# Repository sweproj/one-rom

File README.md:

# One ROM

**[One ROM](https://onerom.org) - One ROM To Rule Them All**

The most flexible ROM replacement for your retro computer.  It is highly configurable and low-cost.  Get them fabbed at JLC for under $5 each in a quantity of 10 or more.

Based on a Raspberry Pi RP2350 (One ROM Fire 🔥) or STM32F4 (One ROM Ice ❄️).

One ROM is available as 24 pin and 28 pin versions, emulating nearly all systems' 24 and 28 pin ROMs, including any possible chip select configurations with a single hardware variants, and can serve different images to multiple ROM sockets simultaneously.

Replaces failed ROMs in Commodore 64s, VIC-20s, PETs, Ataris, BBC, TIs, disk drives and many other types of systems, like pinball machines and music synthesizers.

ROM types replaced:
- 24 pin: 2704, 2708, 2716, 2732, 2316, 2332, 2364
- 28 pin: 2764, 27128, 27256, 27512, 23128, 23256, 23512

As of the latest firmware, One ROM also supports RAM chips of the correct footprint, including the 6116 and 2016 2K SRAM chips.

One ROM was formerly known as Software Defined Retro ROM (SDRR).

## Quick Start

See https://onerom.org/start/

## Key Features

💰 Based on sub-$2 microcontrollers.  **[Choose from Raspberry Pi (Fire 🔥) or STM (Ice ❄️) flavours](docs/MCU-SELECTION.md)**.

⚡ **[Fast](docs/STM32-SELECTION.md)** enough for PETs, VIC-20s, C64s, 1541s, IEEE drives, etc. Support faster systems with higher end microcontroller.

📐 **[Same footprint](docs/images/sdrr-24-pin-side.png)** as original ROMs - doesn't overhang the socket like other solutions.

🔌 **[USB Version](https://onerom.org/prog/)** - no programmer required, program from your browser.

🚀 **[Quick programming](docs/PROGRAMMING.md)** - build and flash in <10 seconds.

🛠️ **[Reflash in situ](docs/PROGRAMMING.md)** - no need to remove the ROM from the host when reprogramming.

⚙️ **[Software configurable](docs/CONFIGURATION.md)** chip select lines - no hardware jumpers required.

💾 Stores up to **[16 ROM images](docs/STM32-SELECTION.md)** of different sizes and chip select configurations.  Image selectable via jumpers.

📦 **[Replace multiple ROMs with one ROM](docs/MULTI-ROM-SETS.md)** a single One ROM can replace up to 3 original ROMs e.g. all of C64 kernel, BASIC, character set.

🔀 **[Dynamic bank switching](docs/MULTI-ROM-SETS.md)** - switch between ROM images on the fly, e.g. different char ROMs.

💻 **[Hackable at runtime](docs/RUNTIME-ACCESS.md)** - change the ROM images being served and access telemetry from the ROM at runtime using **[Airfrog](https://piers.rocks/u/airfrog)** or other SWD probes.

🧩 **[Images combined automatically](docs/CONFIGURATION.md)** - no need to manually build up your own larger PROM image containing multiple retro ROMs.

🏭 **[Two layer PCB](sdrr-pcb/README.md)**, component on single-side, limited BOM for low manufacturing cost/complexity.

🎯 Supports multiple **[STM32F4xxR](docs/STM32-SELECTION.md)** variants: F401, F411, F405, F446 (others can be added).

🔓 **[Open source](LICENSE.md)** software and hardware.

## Introduction

The video below provides an introduction to One ROM:

## Hardware

This is the Fire 24-pin version, hardware revison A.  See [sdrr-pcb](sdrr-pcb/README.md) for the hardware designs and documentation.

<div style="display: flex; justify-content: center; gap: 20px;">
  
</div>

## Documentation

| Topic | Description |
|-------|-------------|
| [Getting Started](docs/GETTING-STARTED.md) | Detailed instructions for flashing your One ROM |
| [Frequently Asked Questions](docs/FAQ.md) | Answers to common questions about One ROM. |
| [Installation](INSTALL.md) | Installation of dependencies. |
| [Programming](docs/PROGRAMMING.md) | How to program One ROM. |
| [Available Configurations](config/README.md#available-configurations) | Various pre-collated ROM collection configurations. |
| [MCU Selection](docs/MCU-SELECTION.md) | How to select the appropriate MCU for your application. |
| [Image Selection](docs/IMAGE-SELECTION.md) | How to tell One ROM which of the installed ROM images to serve. |
| [Image Sets](docs/MULTI-ROM-SETS.md) | How to use a single One ROM to support multiple ROMs simultaneously or to dynamically switch between images. |
| [Configuration](docs/CONFIGURATION.md) | One ROM configuration options. |
| [Runtime Access/Control](docs/RUNTIME-ACCESS.md) | Access and control the One ROM while it is serving ROMs. |
| [Compatibility](docs/COMPATIBILITY.md) | Compatibility with various retro systems. |
| [Logging](docs/LOGGING.md) | How to enable and use One ROM logging. |
| [Technical Summary](docs/TECHNICAL-SUMMARY.md) | Overview of the One ROM architecture, operation and design decisions. |
| [Technical Details](docs/TECHNICAL-DETAILS.md) | Technical details of the One ROM firmware and hardware. |
| [ROMs Glorious ROMs](docs/ROMS-GLORIOUS-ROMS.md) | Everything you ever wanted to know about 23/27 series ROMs but were afraid to ask. |
| [Custom Hardware](docs/CUSTOM-HARDWARE.md) | Guide on designing custom hardware for One ROM. |
| [Build System](docs/BUILD-SYSTEM.md) | How the One ROM build system works. |
| [Voltage Levels](docs/VOLTAGE-LEVELS.md) | How the One ROM supports the required logic voltage levels. |
| [Pi Pico Programmer](docs/PI-PICO-PROGRAMMER.md) | How to use a $5 Raspberry Pi Pico as a programmer for One ROM. |
| [Manufacturing Test](docs/MANUFACTURING-TEST.md) | Information on testing One ROM during manufacturing. |
| [STM32 Clones](docs/STM32-CLONES.md) | Information using STM32 clones with One ROM. |
| [Future Enhancements](docs/FUTURE-ENHANCEMENTS.md) | Possible future enhancements under consideration. |
| [License](LICENSE.md) | One ROM software and hardware licenses. |

## Debugging

The best place to start with debugging is [`Logging`](docs/LOGGING.md).  This will help you see what the One ROM is doing, and why it may not be working as expected.

If you have an [Airfrog](https://piers.rocks/u/airfrog), you can use it to inspect the One ROM firmware and its current state.

If you'd like a hand, raise an issue on the [GitHub issues page](https://github.com/piersfinlayson/software-defined-retro-rom/issues).  Please provide:

- the MCU you are using and the PCB type/revision
- the retro system you are trying to One ROM with
- any logging from One ROM
- ideally, the firmware image, if you are happy to share.

If you have built the firmware yourself, rather than using a pre-built release image, also provide:

- your build configuration
- the output from `make info-detail`.

## License

See [LICENSE](LICENSE.md) for software and hardware licensing information.

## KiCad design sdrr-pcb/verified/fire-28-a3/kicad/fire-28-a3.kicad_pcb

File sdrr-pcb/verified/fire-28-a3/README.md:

# One ROM Fire 28 pin 

**Verified - This design only differs from A2 in correcting the SWD CLK/DIO silkscreen labels.

A3 revision of the 28 pin Fire ROM board.  Combined USB/Pro version with USB-C and SWD header pins.

Very minor difference from revision A2:
- CLK/DIO silkscreen labels swapped to correct positions.

## Contents

- [Schematic](./fire-28-a3-schematic.pdf)
- [Fab Files](fab/)
- [KiCad Design Files](kicad/)
- [Errata](#errata)
- [Notes](#notes)
- [Changelog](#changelog)
- [BOM](#bom)

## Errata

## Notes

## Changelog

## BOM

See fab files.

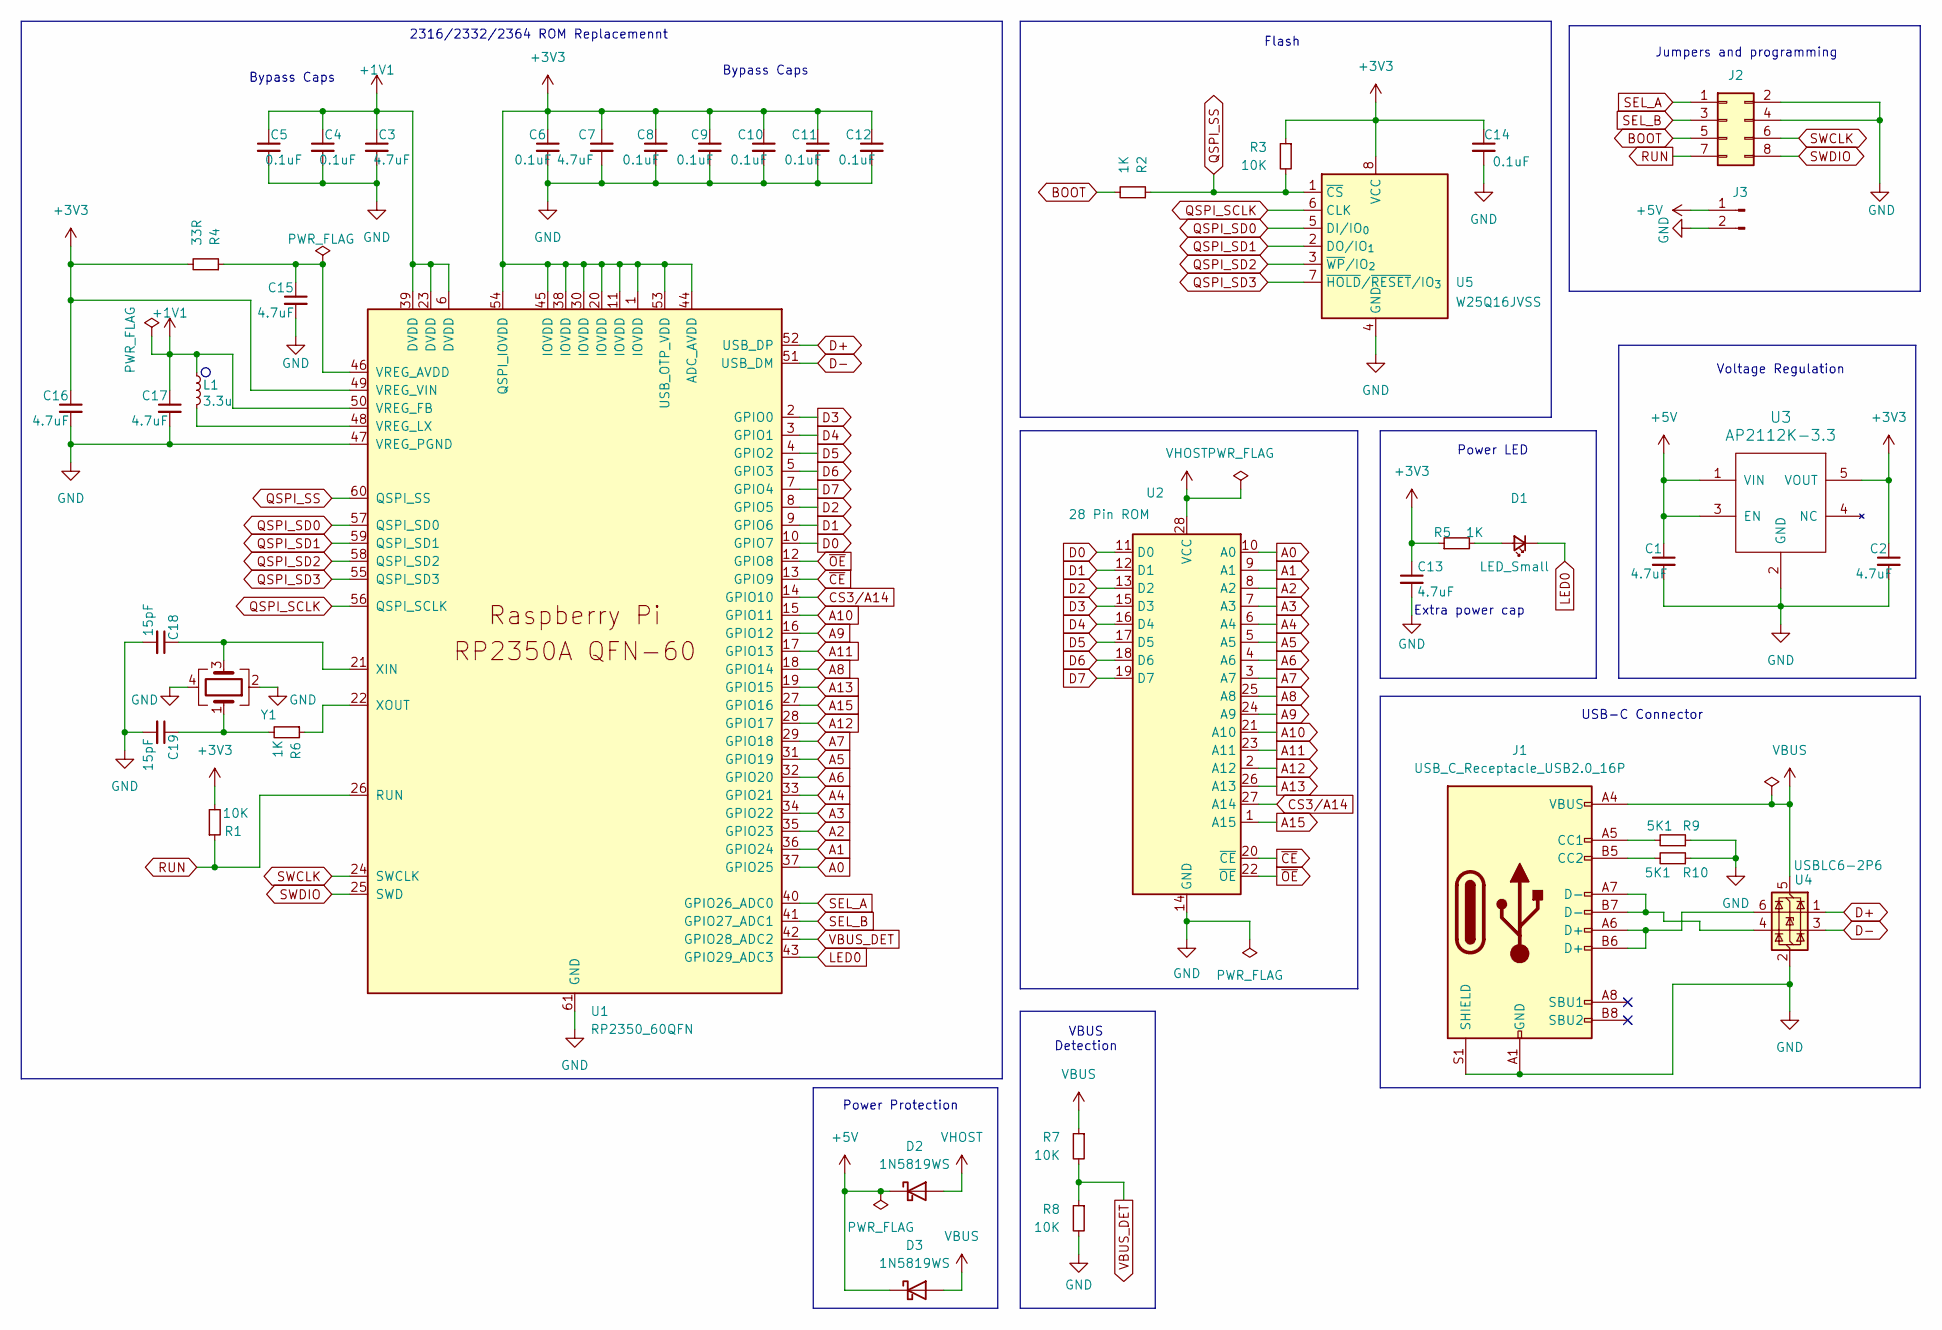
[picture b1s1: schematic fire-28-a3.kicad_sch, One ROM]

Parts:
C1, C2, C3, C7, C13, C15: 4.7uF; C_0402_1005Metric; LCSC C23733
C4, C5, C6, C8, C9, C10, C11, C12, C14: 0.1uF; C_0402_1005Metric; LCSC C1525
C16, C17: 4.7uF; C_0402_1005Metric_small_pads; LCSC C23733
C18, C19: 15pF; C_0402_1005Metric; LCSC C1548
D1: LED_Small; LED_0603_1608Metric; LCSC C2286
D2, D3: 1N5819WS; D_SOD-323; LCSC C191023
J1: USB_C_Receptacle_USB2.0_16P; USB_C_connector_c2765186; LCSC C2765186
J2: Conn_02x04_Odd_Even; PinHeader_2x04_P2.54mm_Vertical custom silkscreen
J3: Conn_01x02_Pin; PinHeader_1x02_P2.54mm_Vertical
L1: 3.3u; L_pol_2016; LCSC C42411119
R1, R3, R7, R8: 10K; R_0402_1005Metric; LCSC C25744
R2, R5, R6: 1K; R_0402_1005Metric; LCSC C11702
R4: 33R; R_0402_1005Metric; LCSC C25105
R9, R10: 5K1; R_0402_1005Metric; LCSC C25905
U1: RP2350_60QFN; RP2350-QFN-60-1EP_7x7_P0.4mm_EP3.4x3.4mm_ThermalVias; LCSC C42411118
U2: 28 Pin ROM; 28 pin rom footprint
U3: AP2112K-3.3; SOT-23-5; LCSC C51118
U4: USBLC6-2P6; SOT-666; LCSC C15999
U5: W25Q16JVSS; Winbond_USON-8-1EP_3x2mm_P0.5mm_EP0.2x1.6mm; LCSC C2843335
Y1: Crystal_GND24; Crystal_SMD_Abracon_ABM8G-4Pin_3.2x2.5mm; LCSC C20625731

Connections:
+1V1: C3.1, C4.1, C5.1, C17.1, L1.1, U1.6 (DVDD), U1.23 (DVDD), U1.39 (DVDD), U1.50 (VREG_FB)
+3V3: C2.1, C6.1, C7.1, C8.1, C9.1, C10.1, C11.1, C12.1, C13.1, C14.1, C16.1, R1.2, R3.1, R4.2, R5.1, U1.1 (IOVDD), U1.11 (IOVDD), U1.20 (IOVDD), U1.30 (IOVDD), U1.38 (IOVDD), U1.44 (ADC_AVDD), U1.45 (IOVDD), U1.49 (VREG_VIN), U1.53 (USB_OTP_VDD), U1.54 (QSPI_IOVDD), U3.5 (VOUT), U5.8 (VCC)
+5V: C1.1, D2.1 (K), D3.1 (K), J3.1, U3.1 (VIN), U3.3 (EN)
A0: U1.37 (GPIO25), U2.10 (A0)
A1: U1.36 (GPIO24), U2.9 (A1)
A2: U1.35 (GPIO23), U2.8 (A2)
A3: U1.34 (GPIO22), U2.7 (A3)
A4: U1.33 (GPIO21), U2.6 (A4)
A5: U1.31 (GPIO19), U2.5 (A5)
A6: U1.32 (GPIO20), U2.4 (A6)
A7: U1.29 (GPIO18), U2.3 (A7)
A8: U1.18 (GPIO14), U2.25 (A8)
A9: U1.16 (GPIO12), U2.24 (A9)
A10: U1.15 (GPIO11), U2.21 (A10)
A11: U1.17 (GPIO13), U2.23 (A11)
A12: U1.28 (GPIO17), U2.2 (A12)
A13: U1.19 (GPIO15), U2.26 (A13)
A15: U1.27 (GPIO16), U2.1 (A15)
BOOT: J2.5, R2.2
CS3/A14: U1.14 (GPIO10), U2.27 (A14)
D0: U1.10 (GPIO7), U2.11 (D0)
D1: U1.9 (GPIO6), U2.12 (D1)
D2: U1.8 (GPIO5), U2.13 (D2)
D3: U1.2 (GPIO0), U2.15 (D3)
D4: U1.3 (GPIO1), U2.16 (D4)
D5: U1.4 (GPIO2), U2.17 (D5)
D6: U1.5 (GPIO3), U2.18 (D6)
D7: U1.7 (GPIO4), U2.19 (D7)
D+: U1.52 (USB_DP), U4.1 (I/O1)
D-: U1.51 (USB_DM), U4.3 (I/O2)
GND: C1.2, C2.2, C3.2, C4.2, C5.2, C6.2, C7.2, C8.2, C9.2, C10.2, C11.2, C12.2, C13.2, C14.2, C15.2, C16.2, C17.2, C18.2, C19.2, J1.A1 (GND), J1.A12 (GND), J1.B1 (GND), J1.B12 (GND), J1.S1 (SHIELD), J2.2, J2.4, J3.2, R8.2, R9.1, R10.1, U1.47 (VREG_PGND), U1.61 (GND), U2.14 (GND), U3.2 (GND), U4.2 (GND), U5.4 (GND), Y1.2, Y1.4
LED0: D1.1 (K), U1.43 (GPIO29_ADC3)
unnamed: C19.1, R6.2, Y1.1
unnamed: D1.2 (A), R5.2
unnamed: J1.A5 (CC1), R9.2
unnamed: J1.B5 (CC2), R10.2
unnamed: J1.A6 (D+), J1.B6 (D+), U4.6 (I/O1)
unnamed: J1.A7 (D-), J1.B7 (D-), U4.4 (I/O2)
unnamed: C15.1, R4.1, U1.46 (VREG_AVDD)
unnamed: L1.2, U1.48 (VREG_LX)
unnamed: C18.1, U1.21 (XIN), Y1.3
unnamed: R6.1, U1.22 (XOUT)
QSPI_SCLK: U1.56 (QSPI_SCLK), U5.6 (CLK)
QSPI_SD0: U1.57 (QSPI_SD0), U5.5 (DI/IO_{0})
QSPI_SD1: U1.59 (QSPI_SD1), U5.2 (DO/IO_{1})
QSPI_SD2: U1.58 (QSPI_SD2), U5.3 (~WP/IO_{2})
QSPI_SD3: U1.55 (QSPI_SD3), U5.7 (~HOLD/~RESET/IO_{3})
QSPI_SS: R2.1, R3.2, U1.60 (QSPI_SS), U5.1 (~CS)
RUN: J2.7, R1.1, U1.26 (RUN)
SEL_A: J2.1, U1.40 (GPIO26_ADC0)
SEL_B: J2.3, U1.41 (GPIO27_ADC1)
SWCLK: J2.6, U1.24 (SWCLK)
SWDIO: J2.8, U1.25 (SWD)
VBUS: D3.2 (A), J1.A4 (VBUS), J1.A9 (VBUS), J1.B4 (VBUS), J1.B9 (VBUS), R7.1, U4.5 (VBUS)
VBUS_DET: R7.2, R8.1, U1.42 (GPIO28_ADC2)
VHOST: D2.2 (A), U2.28 (VCC)
~CE: U1.13 (GPIO9), U2.20 (~CE)
~OE: U1.12 (GPIO8), U2.22 (~OE)

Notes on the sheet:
USB-C Connector
Voltage Regulation
Extra power cap
2316/2332/2364 ROM Replacemennt
Bypass Caps
Power LED
Power Protection
VBUS Detection
Flash
Jumpers and programming

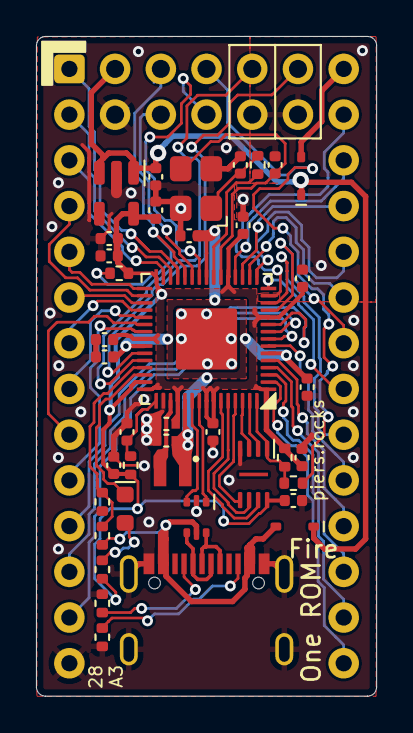
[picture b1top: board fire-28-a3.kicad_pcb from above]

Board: 2 copper layers, 18.9 x 36.7 mm, 42 parts (0 on the bottom side), 58 nets.

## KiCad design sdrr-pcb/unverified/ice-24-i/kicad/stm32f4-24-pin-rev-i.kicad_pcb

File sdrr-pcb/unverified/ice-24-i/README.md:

# One ROM Ice USB H2 24 Pin 

**Unverified**: Similar to ice-24-c.

There is a single set of gerbers, and two sets of POS/BOM files:
- One for the STM32F411RET6 MCU.
- One for the STM32F446RCT6 MCU.

To create the BOM for an alternate MCU, replace the microcontroller part number.  For the STM32F405RET6, you must also replace RC4/RC5/C9 - see the schematic for details.

## Contents

- [Schematic](ice-24-i-schematic.pdf)
- [Fab Files and BOM](fab/)
- [KiCad Design Files](kicad/)
- [Errata](#errata)
- [Notes](#notes)
- [Changelog](#changelog)

## Errata

## Notes

## Changelog

- Move to 1N5819 diodes from MSK4005 (better availability and JLC basic part)
- Moved programming header to top left, replacing Sel pins C-E
- Reduced rom pin hole and ring size
- Reduced silkscreen markings on the top side

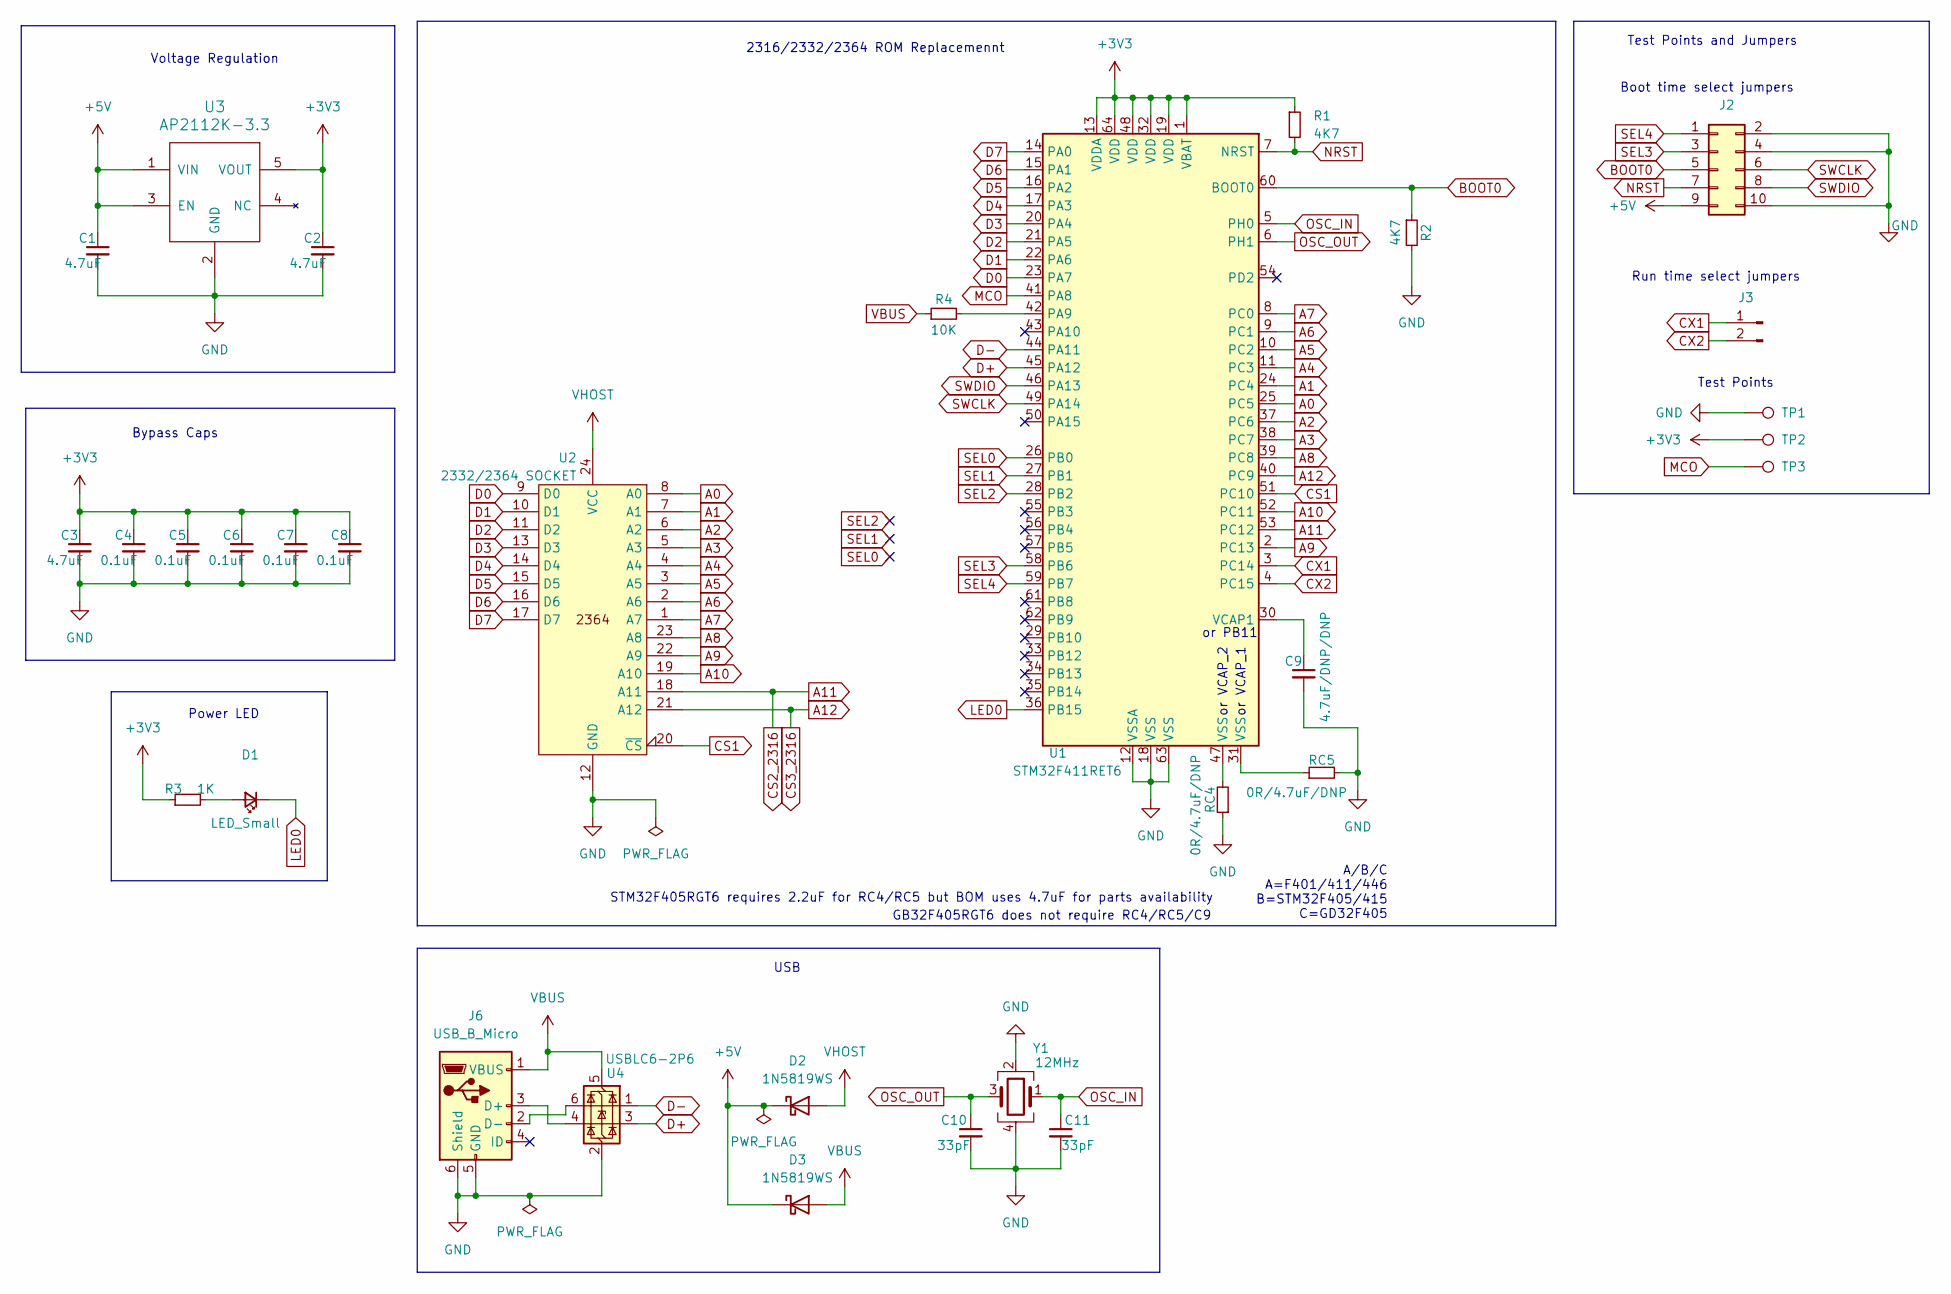
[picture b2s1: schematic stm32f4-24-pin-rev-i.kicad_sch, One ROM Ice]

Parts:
C1, C2, C3: 4.7uF; C_0402_1005Metric; LCSC C23733
C4, C5, C6, C7, C8: 0.1uF; C_0402_1005Metric; LCSC C1525
C9: 4.7uF/DNP/DNP; C_0402_1005Metric; LCSC C23733
C10, C11: 33pF; C_0402_1005Metric; LCSC C1562
D1: LED_Small; LED_0603_1608Metric; LCSC C2286
D2, D3: 1N5819WS; D_SOD-323; LCSC C191023
J2: Conn_02x05_Odd_Even; PinHeader_2x05_P2.54mm_Vertical custom silkscreen
J3: Conn_01x02_Pin; PinHeader_1x02_P2.54mm_Vertical
J6: USB_B_Micro; USB_Micro-B_micro_xnj_073_C404969; LCSC C404969
R1, R2: 4K7; R_0402_1005Metric; LCSC C25900
R3: 1K; R_0402_1005Metric; LCSC C11702
R4: 10K; R_0402_1005Metric; LCSC C25744
RC4, RC5: 0R/4.7uF/DNP; C_0402_1005Metric; LCSC C17168
TP1, TP2, TP3: TestPoint; 1mm smd test point small ss
U1: STM32F411RET6; LQFP-64_10x10mm_P0.5mm; LCSC C94355
U2: 2332/2364 SOCKET; 2x12 dip pin output 600mil centres no ss
U3: AP2112K-3.3; SOT-23-5; LCSC C51118
U4: USBLC6-2P6; SOT-666; LCSC C15999
Y1: 12MHz; Crystal_SMD_3225-4Pin_3.2x2.5mm; LCSC C9002

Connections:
+3V3: C2.1, C3.1, C4.1, C5.1, C6.1, C7.1, C8.1, R1.1, R3.1, TP2.1, U1.1 (VBAT), U1.13 (VDDA), U1.19 (VDD), U1.32 (VDD), U1.48 (VDD), U1.64 (VDD), U3.5 (VOUT)
+5V: C1.1, D2.1 (K), D3.1 (K), J2.9, U3.1 (VIN), U3.3 (EN)
A0: U1.25 (PC5), U2.8 (A0)
A1: U1.24 (PC4), U2.7 (A1)
A2: U1.37 (PC6), U2.6 (A2)
A3: U1.38 (PC7), U2.5 (A3)
A4: U1.11 (PC3), U2.4 (A4)
A5: U1.10 (PC2), U2.3 (A5)
A6: U1.9 (PC1), U2.2 (A6)
A7: U1.8 (PC0), U2.1 (A7)
A8: U1.39 (PC8), U2.23 (A8)
A9: U1.2 (PC13), U2.22 (A9)
A10: U1.52 (PC11), U2.19 (A10)
A11: U1.53 (PC12), U2.18 (A11)
A12: U1.40 (PC9), U2.21 (A12)
BOOT0: J2.5, R2.1, U1.60 (BOOT0)
CS1: U1.51 (PC10), U2.20 (~CS)
CX1: J3.1, U1.3 (PC14)
CX2: J3.2, U1.4 (PC15)
D0: U1.23 (PA7), U2.9 (D0)
D1: U1.22 (PA6), U2.10 (D1)
D2: U1.21 (PA5), U2.11 (D2)
D3: U1.20 (PA4), U2.13 (D3)
D4: U1.17 (PA3), U2.14 (D4)
D5: U1.16 (PA2), U2.15 (D5)
D6: U1.15 (PA1), U2.16 (D6)
D7: U1.14 (PA0), U2.17 (D7)
D+: U1.45 (PA12), U4.3 (I/O2)
D-: U1.44 (PA11), U4.1 (I/O1)
GND: C1.2, C2.2, C3.2, C4.2, C5.2, C6.2, C7.2, C8.2, C9.2, C10.2, C11.2, J2.2, J2.4, J2.10, J6.5 (GND), J6.6 (Shield), R2.2, RC4.1, RC5.2, TP1.1, U1.12 (VSSA), U1.18 (VSS), U1.63 (VSS), U2.12 (GND), U3.2 (GND), U4.2 (GND), Y1.2, Y1.4
LED0: D1.1 (K), U1.36 (PB15)
MCO: TP3.1, U1.41 (PA8)
NRST: J2.7, R1.2, U1.7 (NRST)
unnamed: D1.2 (A), R3.2
unnamed: J6.3 (D+), U4.4 (I/O2)
unnamed: J6.2 (D-), U4.6 (I/O1)
unnamed: RC4.2, U1.47 (VSS)
unnamed: RC5.1, U1.31 (VSS)
unnamed: R4.2, U1.42 (PA9)
unnamed: C9.1, U1.30 (VCAP1)
OSC_IN: C11.1, U1.5 (PH0), Y1.1
OSC_OUT: C10.1, U1.6 (PH1), Y1.3
SEL0: U1.26 (PB0)
SEL1: U1.27 (PB1)
SEL2: U1.28 (PB2)
SEL3: J2.3, U1.58 (PB6)
SEL4: J2.1, U1.59 (PB7)
SWCLK: J2.6, U1.49 (PA14)
SWDIO: J2.8, U1.46 (PA13)
VBUS: D3.2 (A), J6.1 (VBUS), R4.1, U4.5 (VBUS)
VHOST: D2.2 (A), U2.24 (VCC)

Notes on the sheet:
or VCAP_1
or VCAP_2
Run time select jumpers
USB
Voltage Regulation
2316/2332/2364 ROM Replacemennt
Power LED
or PB11
GB32F405RGT6 does not require RC4/RC5/C9
Test Points
Bypass Caps
Boot time select jumpers
A/B/C A=F401/411/446 B=STM32F405/415 C=GD32F405
Test Points and Jumpers
STM32F405RGT6 requires 2.2uF for RC4/RC5 but BOM uses 4.7uF for parts availability

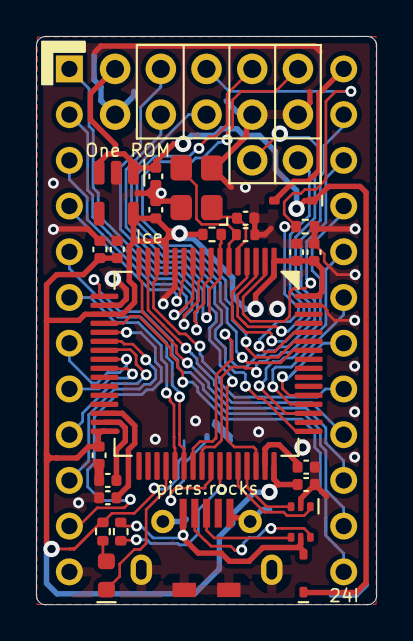
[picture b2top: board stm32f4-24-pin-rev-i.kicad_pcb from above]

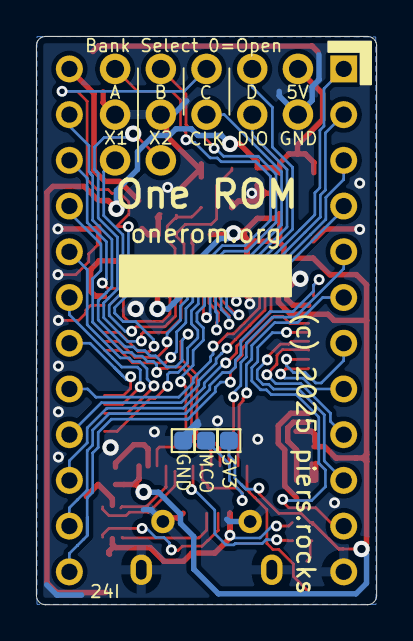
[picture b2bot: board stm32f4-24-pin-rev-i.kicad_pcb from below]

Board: 2 copper layers, 18.9 x 31.6 mm, 31 parts (3 on the bottom side), 48 nets.

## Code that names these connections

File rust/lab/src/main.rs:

//! One ROM Lab firmware

// Copyright (c) 2025 Piers Finlayson <piers@piers.rocks>
//
// MIT licence

#![no_std]
#![no_main]
#![feature(type_alias_impl_trait)]
#![feature(impl_trait_in_assoc_type)]

extern crate alloc;

#[allow(unused_imports)]
use log::{debug, error, info, trace, warn};

use embassy_executor::Spawner;
use embassy_executor::main as embassy_main;
use embassy_stm32::gpio::Flex;
use embassy_stm32::rcc::clocks;

#[cfg(feature = "repeat")]
use embassy_time::Timer;

use embedded_alloc::LlffHeap as Heap;
#[cfg(feature = "usb")]
use panic_probe as _;
#[cfg(not(feature = "usb"))]
use panic_rtt_target as _;

#[cfg(feature = "control")]
mod control;
mod error;
mod info;
mod logs;
mod rcc;
mod rom;
mod types;
#[cfg(feature = "usb")]
mod usb;

pub use error::Error;
pub use rom::{Id as RomId, Rom};

use info::{LAB_RAM_INFO, PKG_VERSION};

#[global_allocator]
static HEAP: Heap = Heap::empty();

#[cortex_m_rt::pre_init]
unsafe fn pre_init() {
    #[cfg(feature = "usb")]
    usb::check_bootloader_flag();
    info::copy_lab_ram_info();
}

#[embassy_main]
async fn main(_spawner: Spawner) {
    // Initialize the heap allocator
    {
        use core::mem::MaybeUninit;
        const HEAP_SIZE: usize = 1024;
        static mut HEAP_MEM: [MaybeUninit<u8>; HEAP_SIZE] = [MaybeUninit::uninit(); HEAP_SIZE];
        unsafe { HEAP.init(&raw mut HEAP_MEM as usize, HEAP_SIZE) }
    }

    // Set up clock config
    let mut config = embassy_stm32::Config::default();
    #[cfg(feature = "usb")]
    rcc::configure_hse_usb(&mut config);
    #[cfg(not(feature = "usb"))]
    rcc::configure_hsi(&mut config);

    // Get peripherals
    let p = embassy_stm32::init(config);

    // Configure clocks
    let clocks = clocks(&p.RCC);

    // Init USB/logging
    #[cfg(feature = "usb")]
    {
        let usb_device = usb::Usb::new(p.USB_OTG_FS, p.PA12, p.PA11);
        usb::run(_spawner, usb_device);
        usb::init_logger();
    }
    #[cfg(not(feature = "usb"))]
    logs::init_rtt();

    info!("-----");
    info!("One ROM Lab v{}", PKG_VERSION);
    info!("Copyright (c) 2025 Piers Finlayson");

    // Log clocks
    info!("-----");
    match clocks.sys.to_hertz() {
        Some(hz) => debug!("SYSCLK: {hz}"),
        None => warn!("SYSCLK: Unknown"),
    }

    debug!(
        "One ROM Lab Flash Info address: {:#010X}",
        &info::LAB_FLASH_INFO as *const _ as usize
    );
    #[allow(static_mut_refs)]
    unsafe {
        debug!(
            "One ROM Lab RAM Info address:   {:#010X}",
            &LAB_RAM_INFO as *const _ as usize
        );
    }

    // Collate the address and data pins
    let addr_pins = [
        Flex::new(p.PC5),
        Flex::new(p.PC4),
        Flex::new(p.PC6),
        Flex::new(p.PC7),
        Flex::new(p.PC3),
        Flex::new(p.PC2),
        Flex::new(p.PC1),
        Flex::new(p.PC0),
        Flex::new(p.PC8),
        Flex::new(p.PC13),
        Flex::new(p.PC11),
        Flex::new(p.PC12),
        Flex::new(p.PC9),
        Flex::new(p.PC10), // 2364 CS pin, set as "A13"
    ];
    let data_pins = [
        Flex::new(p.PA7),
        Flex::new(p.PA6),
        Flex::new(p.PA5),
        Flex::new(p.PA4),
        Flex::new(p.PA3),
        Flex::new(p.PA2),
        Flex::new(p.PA1),
        Flex::new(p.PA0),
    ];

    // Create the ROM object
    let mut rom = Rom::new(addr_pins, data_pins);
    unsafe {
        LAB_RAM_INFO.rom_data = rom.buf.as_ptr() as *const core::ffi::c_void;
    }
    rom.init();

    #[cfg(feature = "control")]
    {
        let mut control = control::Control::new(rom);
        control.run().await;
    }

    #[cfg(feature = "qa")]
    {
        info!("QA mode");
        #[cfg(feature = "usb")]
        info!("Press `d` to enter DFU mode");
        loop {
            #[cfg(not(feature = "usb"))]
            match rom.read_rom().await {
                Some(_) => info!("ROM read successfully"),
                None => info!("Failed to read ROM"),
            }
            #[cfg(feature = "usb")]
            match embassy_time::with_timeout(embassy_time::Duration::from_secs(5), usb::recv_key())
                .await
            {
                Ok(key) => {
                    if key == b'd' {
                        info!("Entering DFU mode...");
                        usb::enter_dfu_mode().await;
                    }
                }
                Err(_) => (),
            }
            #[cfg(not(feature = "usb"))]
            embassy_time::Timer::after_secs(5).await;
            info!("Reading ROM...");
        }
    }

    #[cfg(not(any(feature = "control", feature = "qa")))]
    {
        loop {
            match rom.read_rom().await {
                Some(_) => break,
                None => info!("Failed to read ROM"),
            }

            #[cfg(feature = "oneshot")]
            {
                info!("Done");
                return;
            }
            #[cfg(feature = "repeat")]
            {
                info!("Waiting 5 seconds before reading again");
                Timer::after_secs(5).await;
            }
        }
    }
}

#[cfg(all(feature = "control", feature = "oneshot"))]
compile_error!("Features 'control' and 'oneshot' are mutually exclusive");

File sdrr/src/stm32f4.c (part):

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    }
}

// Set up interrupt to fire when VBUS sensed on PA9
void setup_vbus_interrupt(void) {
    // Does NOT currently honour configured VBUS port/pin - assumes PA9
    if (sdrr_info.extra->vbus_pin != 9 ||
        sdrr_info.extra->usb_port != PORT_A) {
        LOG("!!! Invalid USB port or pin for VBUS detect - not enabling USB DFU");
        return;
    }

    // Set PA9 pull-down
    GPIOA_PUPDR &= ~(0b11 << (2 * 9));
    GPIOA_PUPDR |= (0b10 << (2 * 9)); // Pull-down

    // Configure interrupt on rising edge on PA9 to sense VBUS
    RCC_APB2ENR |= RCC_APB2ENR_SYSCFGEN;
    GPIOA_MODER &= ~GPIOA_MODER_PA9_MASK;
    SYSCFG_EXTICR3 &= ~SYSCFG_EXTICR3_PA9_MASK;
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    EXTI_IMR |= EXTI_IMR_MR9;
    NVIC_ISER0 |= NVIC_ISER0_EXTI9_5;

    // Now, just double check whether PA9 is already high.  If so, directly
    // enter the bootloader, as we may have missed the interrupt if VBUS was
    // already present.  This is typical if One ROM is powered on from USB.
    //
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    }
}

// VBUS (PA9) interrupt Handler
void vbus_connect_handler(void) {
    EXTI_PR = EXTI_PR_PR9;

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    //
    uint32_t gpioa_moder = 0;
    uint32_t gpioa_pupdr = 0;
    uint32_t gpioa_ospeedr = 0x0000AAAA;    // PA0-7 fast speed, not high
                                            // speed, to ensure V(OL) max 0.4V

    if (sdrr_info.swd_enabled) {
        gpioa_moder |= 0x28000000; // Set 13/14 as AF
        gpioa_pupdr |= 0x24000000; // Set pull-up on PA13, down on PA14
    }

    if (sdrr_info.mco_enabled) {
        gpioa_moder |= 0x00020000; // Set PA8 as AF
        gpioa_ospeedr |= 0x00030000; // Set PA8 to very high speed
    }
    
    GPIOA_MODER = gpioa_moder;
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    // GPIOB and GPIOC
    //

    // Set PB0-2 and PB7 as inputs, with pull-downs.  HW rev D only uses
    // PB0-2 but as PB7 isn't connected we can set it here as well.
    // We do this early doors, so the internal pull-downs will have settled
    // before we read the pins.
    // TODO the code to set PU/PD should be retired (and then tested as the
    // PU/PD is now done in check_sel_pins()).
    GPIOB_MODER = 0;  // Set all GPIOs as inputs
    GPIOB_PUPDR &= ~0x0000C03F;  // Clear pull-up/down for PB0-2 and PB7
    GPIOB_PUPDR |= 0x0000802A;   // Set pull-downs on PB0-2 and PB7

    GPIOC_MODER = 0;  // Set all GPIOs as inputs

#if defined(MCO2)
    uint32_t gpioc_moder = GPIOC_MODER;
    gpioc_moder &= ~(0b11 << (9 * 2));  // Clear bits for PC9
    gpioc_moder |= 0x00080000; // Set PC9 as AF
    GPIOC_MODER = gpioc_moder;
    GPIOC_OSPEEDR |= 0x000C0000; // Set PC9 to very high speed
    GPIOC_OTYPER &= ~(0b1 << 9);  // Set as push-pull
#else // !MCO2
    GPIOC_PUPDR = 0; // No pull-up/down
#endif // MCO2
}

// Common setup for status LED output using PB15 (inverted logic: 0=on, 1=off)
void setup_status_led(void) {
    if (sdrr_info.pins->status_port != PORT_B) {
        LOG("!!! Status port not B - not using");
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        RCC_AHB1ENR |= RCC_AHB1ENR_GPIOBEN; // Enable GPIOB clock
        
        uint8_t pin = sdrr_info.pins->status;
        GPIOB_MODER &= ~(0x3 << (pin * 2));  // Clear bits for PB15
        GPIOB_MODER |= (0x1 << (pin * 2));   // Set as output
        GPIOB_OSPEEDR |= (0x3 << (pin * 2)); // Set speed to high speed
        GPIOB_OTYPER &= ~(0x1 << pin);       // Set as push-pull
        GPIOB_PUPDR &= ~(0x3 << (pin * 2));  // No pull-up/down
        
        GPIOB_BSRR = (1 << pin); // Start with LED off (PB15 high)
    }
}

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#endif // HSI_TRIM
    LOG("PLL MNPQ: %d/%d/%d/%d", PLL_M, PLL_N, PLL_P, PLL_Q);
    if (sdrr_info.mco_enabled) {
        LOG("MCO: enabled - PA8");
    } else {
        LOG("MCO: disabled");
    }
#if defined(MCO2)
    LOG("MCO2: %s - PC9", enabled);
#endif // MCO2

#endif // BOOT_LOGGING
}

// Sets up the MCO (clock output) on PA8, to the value provided
void setup_mco(void) {
    uint8_t mco = RCC_CFGR_MCO1_PLL;

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    RCC_AHB1ENR |= (1 << 0);

    uint32_t gpioa_moder = GPIOA_MODER;
    gpioa_moder &= ~(0b11 << (8 * 2));  // Clear bits for PA8
    gpioa_moder |= (0b10 << (8 * 2));   // Set as AF
    GPIOA_MODER = gpioa_moder;
    GPIOA_OSPEEDR |= (0b11 << (8 * 2));  // Set speed to very high speed
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
#if defined(MCO2)
    uint32_t gpioc_moder = GPIOC_MODER;
    gpioc_moder &= ~(0b11 << (9 * 2));  // Clear bits for PC9
    gpioc_moder |= (0b10 << (9 * 2));   // Set as AF
    GPIOC_MODER = gpioc_moder;
    GPIOC_OSPEEDR |= (0b11 << (9 * 2));  // Set speed to very high speed
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
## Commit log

2025-09-06 Release v0.4.2 (One ROM Lab) (#26)
    * First Lab version
    * uprev release and fix up lab to read
    * add rom database
    * add many more roms
    * rewrite rom detection, to detect any supported ROM type
    * improve logging when no ROM or empty ROM connected
2025-09-07 fix features
2025-09-09 add getting started guide
2025-09-09 make images good sizes
2025-09-09 better image
2025-09-09 add one rom lab video
2025-09-10 Update PI-PICO-PROGRAMMER.md (#27)
2025-09-12 fix entering bootloader and add dfu-flash
2025-09-12 Add USB_DFU to enter DFU when USB connected
2025-09-12 DFU only for STM32F4
2025-09-12 enter bootloader if powered from USB - no interrupt
2025-09-12 add dfu-util
2025-09-20 add rev H (USB)
2025-09-20 add usb dfu support (untested)
2025-09-28 get usb support working
2025-09-28 add placeholder site
2025-09-28 Update artifact upload path in static.yml
    Change artifact upload path to './site' for GitHub Pages deployment.
2025-09-28 add usb programmer
2025-09-28 update changelog
2025-09-28 update metadata
2025-09-28 tweak text
2025-09-28 add how it works
2025-09-28 update text
2025-09-29 improve text
2025-09-29 add USB DFU hw (24-h)
2025-09-29 update 0.4.3 changelog
2025-09-29 add local file usb programming option
2025-09-29 add firmware checks
2025-09-29 correct install instructions
2025-09-29 update programmer
2025-09-29 update docker containers
2025-09-29 improve usb programmer
2025-09-30 next release will be 0.4.4
2025-09-30 change releasr artifact handling
2025-09-30 add linux instructions
2025-09-30 add pre-built tab
2025-09-30 update site
2025-09-30 improve release handling
2025-09-30 Add manifest and update releases list for v0.4.4
2025-09-30 add readme
2025-09-30 correct no destestmax description
2025-09-30 update pre-built images
2025-09-30 get pre-built images working
2025-09-30 add cors health check
2025-09-30 add social media card info
2025-09-30 update social media image
2025-09-30 improve linux instructions
2025-09-30 improve site
2025-09-30 add third-party, set and bank configs
2025-09-30 alphabetically sort configs
2025-09-30 correct hw rev g jumpers
2025-09-30 add hw rev h jumpers
2025-09-30 update mcu selection
2025-09-30 improve config descriptions
2025-09-30 clarify
2025-09-30 move site to one-rom-site repo
2025-10-02 new pcbs
2025-10-07 Release v0.5.0 (#33)
    See Release v0.5.0 for description
2025-10-07 Add manifest and update releases list for v0.5.0
2025-10-07 fix no roms blink pattern
2025-10-07 update release notes
2025-10-08 correct RE board capacities
2025-10-08 Add Atari 800 XL BASIC ROM
2025-10-08 add atari
2025-10-08 get sourceforge downloads working
2025-10-13 Release v0.5.1 - 28 pin prototype and major overhaul of metadata and ROM image data code (#35)
    * auto-generate rom type information
    * auto-generate rom type information
    * move over to auto-generated PCB revision code
    * retire sdrr-common
    * get onerom-config working with wasm
    * get firmware ready to serve 23128/27128
2025-10-13 Add manifest and update releases list for v0.5.1
2025-10-14 v0.,5.2 - add onerom-fw cli tool (and fix nasty sdrr-fw-parser bug preventing dynamically generated images from being parsed) (#36)
    * improve gen testing
    * improved gen (and config) testing
    * more validation - rom pins and flash space
    * add description
    * initial empty build image script
    * start new rom-config dir
2025-10-14 Add manifest and update releases list for v0.5.2
2025-10-20 add workflow
2025-10-20 improve
2025-10-20 try again
2025-10-20 try a different working dir
2025-10-21 add build-studio workflow
2025-10-21 remove msi workflow
2025-10-21 fix linux deps
2025-10-21 get packing working in CI
2025-10-24 allow workflows manual triggering
2025-10-24 Release v0.5.3 - added One ROM Studio v0.1.0 - see https://onerom.org/studio/ (#42)
2025-10-24 Add manifest and update releases list for v0.5.3
2025-11-12 Release v0.5.4 (#51)
    * move to 0.5.4
    * fix #re
    * note was/site/images updates required
    * uprev studio to 0.1.1 development
    * add extra rom method
    * add blank config (already added to images)
2025-11-12 Add manifest and update releases list for v0.5.4
2025-11-12 fix release manifest generation
2025-11-12 fix naming of usb-h
2025-11-13 update manifest
2025-11-13 regenerate release
2025-11-13 move to common Ice H/H2 variant
2025-11-13 add usb-b
2025-11-18 Release v0.5.5 (#55)
    * first attempt at autonomous mode
    * basically working pio/dma implementation with 2332 C64 char ROM
    * only call piorom() on RP2350
    * faster pio/dma algorithm
    * enable pio/dma
    * have dual CS working, char rom serving at 69MHz, currently set to single CS
2025-11-19 fix default alg comment
2025-11-19 Add manifest and update releases list for v0.5.5
2025-11-20 update pico instructions
2025-11-23 update one rom fire c64 demo
2025-11-24 remove cs_values
2025-11-24 force static linking
2025-11-24 forcing static link via build.rs doesn't work
2025-11-24 statically link vcruntime
2025-11-25 fix #57
2025-11-26 init DMA ch 1 read_addr to first byte of ROM table
2025-11-29 start qr code
2025-11-29 update lab to add qa setting
2025-12-02 add another 5 cycle version
2025-12-02 add fire-28-a
2025-12-09 Firmware release 0.5.6, Studio 0.1.4 (#61)
    * support local rom files
    * support 2716 and 2732
    * update changelog
    * fix cs line handling
    * add 27 series tests
    * remove rom.pio file as it doesn't provide the actual used PIO code
2025-12-09 Add manifest and update releases list for v0.5.6
2025-12-09 fix 2716/2732 CE/OE pins
2025-12-09 Add manifest and update releases list for v0.5.7
2025-12-11 update quickstart
2025-12-12 Firmware Release v0.5.8 (#64)
    * increment version number
    * support >= 2716 and 2316 24 and 28 pin ROM types using PIO algorithm
    * support 28 pin roms
    * see error output from tests
    * fix test program - allocate correct size for rom image
    * add ice-24-i
2025-12-12 add fire-28-a releases to ci
2025-12-12 0.1.5 includes fire-28-a
2025-12-12 Add manifest and update releases list for v0.5.8
2025-12-12 fix ci to build 24/28 configs for correct hardware
2025-12-15 jlc have changed orientation of micro USB connector?
2025-12-20 add fire-24-c firmware support
2025-12-20 add support for images directly in json config files
2025-12-20 start of a config building implementation directly within studio
2025-12-29 build studio on linux arm64 host
2025-12-30 Add support for building on ARM64 Windows, an ARM64 Windows One ROM Studio, and remote code signing server
2025-12-31 Correctly bundle arm64 Windows binary in arm64 labelled installer
2025-12-31 get linux builds working on ubuntu x86_64 and arm64 and debian x86_64
2025-12-31 try ubuntu 24.04
2025-12-31 new script to build all platforms/architectures
2025-12-31 add 231024 to onerom-config crate
2025-12-31 onerom-gen 0.2.3
2025-12-31 sdrr-fw-parser 0.5.7
2025-12-31 onerom-fw-0.1.5
2025-12-31 use new package versions
2025-12-31 fix broken test
2025-12-31 update for new packages
2025-12-31 update rom schema
2025-12-31 move fire-28-a to verified
2025-12-31 move h3 to verified
2026-01-01 add ice-24-i
2026-01-01 add ice-24-i support
2026-01-01 use PIO_CONFIG_SLOW_CLOCK_CHAR by default for PIO builds
2026-01-01 back out SLOW_CLOCK_CHAR as it will be incompatible in some cases
2026-01-01 add hw revisions
2026-01-01 reorder tests
2026-01-01 add fire-28-a3
2026-01-01 prepare for 0.5.9
2026-01-01 update build instructions for mac
2026-01-01 Add manifest and update releases list for v0.5.9
2026-01-01 prepare for 0.1.6
2026-01-01 improve build scripts
2026-01-01 get ready for next releases
2026-01-01 get ready for next release
2026-01-01 back out fire-24-c as verified hw design
2026-01-03 Support fire-24-c, PIO multi-ROM sets and move RAM ROM table to RAM base (0x2000_0000) (#79)
    * tentative fix to both #76 issues
    * fix PIO serving for non contiguous CS lines
    * promote fire-24-c to verified, and make recommended revision
    * get ci working properly on mac
    * correct contiguity writeup
    * correctly store multi-ROM sets for PIO serving mode
2026-01-03 update lock file
2026-01-03 Add manifest and update releases list for v0.5.10
2026-01-03 Update release readme
2026-01-05 add fire-24-d unverified
2026-01-05 add unverified ice-24-j
2026-01-05 improve documentation
2026-01-06 add Fire 28 pin version of Lab for 28 pin ROM validation
2026-01-07 get 24 pin ice qa version working
2026-01-10 add fire-40-a, a 40 pin 27c400 16-bit ROM prototype
2026-01-10 add jlc query
2026-01-11 add 32 and 40 pin rom types
2026-01-11 prepare for commiting new crates
2026-01-11 publish new crates
2026-01-11 update schema
2026-01-11 fix rust tests
2026-01-11 onerom-studio needs to use crates.io
2026-01-11 fix crate dependencies
2026-01-14 Add support for runtime and One ROM Studio configurable firmware configuration. (#87)
    See pull request #87 for more details.
2026-01-14 Add manifest and update releases list for v0.6.0
2026-01-14 move fire-28-a rev a3 to verified and recommended
2026-01-15 update studio copyright statement
2026-01-19 Merge One RAM prototype code into main. (#98)
    * First working and reliable RAM serving implementation - VIC-20 boots
    * refactor PIO code - this is mid-refactor, RAM function tested working
    * refactor PIO assembly helper macros and RAM PIO0:0
    * add DEBUG_BUILD
    * refactor PIO1 (working)
    * Reduce stack space required by pio assembler
2026-01-19 uprev to 0.6.1
2026-01-19 comment RAM algorithm
2026-01-20 improve RAM algorithm commenting
2026-01-20 move fire-24-d and ice-24-j to verified
2026-01-21 use better display names
2026-01-22 improve docs
2026-01-22 add info on panelising boards
2026-01-22 udpate with extra steps
2026-01-22 Fix 2732 ROM serving, and refactor test scripts (#104)
2026-01-22 Releases 0.6.1 (#105)
    * fix #90
    * update copyright
    * fix fire-24-d image select jumpers
    * add swd sel jumper support for ice boards
    * new verified hardware
    * partial test refactoring to deal with CS lines - tests still run
2026-01-22 Add manifest and update releases list for v0.6.1
2026-01-25 add rp2354 variant of fire d boards
2026-01-25 add 24 rev E
2026-01-26 add fire-28-a3 kicad files
2026-01-27 Add release 0.6.2 - first PIO RAM serving algorithm for Fire 24 C/D (#113)
    * create 40 pin config file - tests run
    * make rams configurable using config files
    * get tests running in 0.7.0 branch
    * further ram improvements
    * get preloading data to RAM working
    * Free up 512KB on RP2350 for chip image
2026-01-27 publish new crate versions
2026-01-27 add fire-40-a to ci build-images.sh
2026-01-27 Add manifest and update releases list for v0.6.2
2026-01-28 Add SRAM /OE behaviour note
2026-01-28 update board recommendations (Fire over Ice)

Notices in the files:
sdrr/src/stm32f4.c:
MIT License
sdrr-pcb/unverified/ice-24-i/kicad/stm32f4-24-pin-rev-i.kicad_pcb:
(c) 2025 piers.rocks
